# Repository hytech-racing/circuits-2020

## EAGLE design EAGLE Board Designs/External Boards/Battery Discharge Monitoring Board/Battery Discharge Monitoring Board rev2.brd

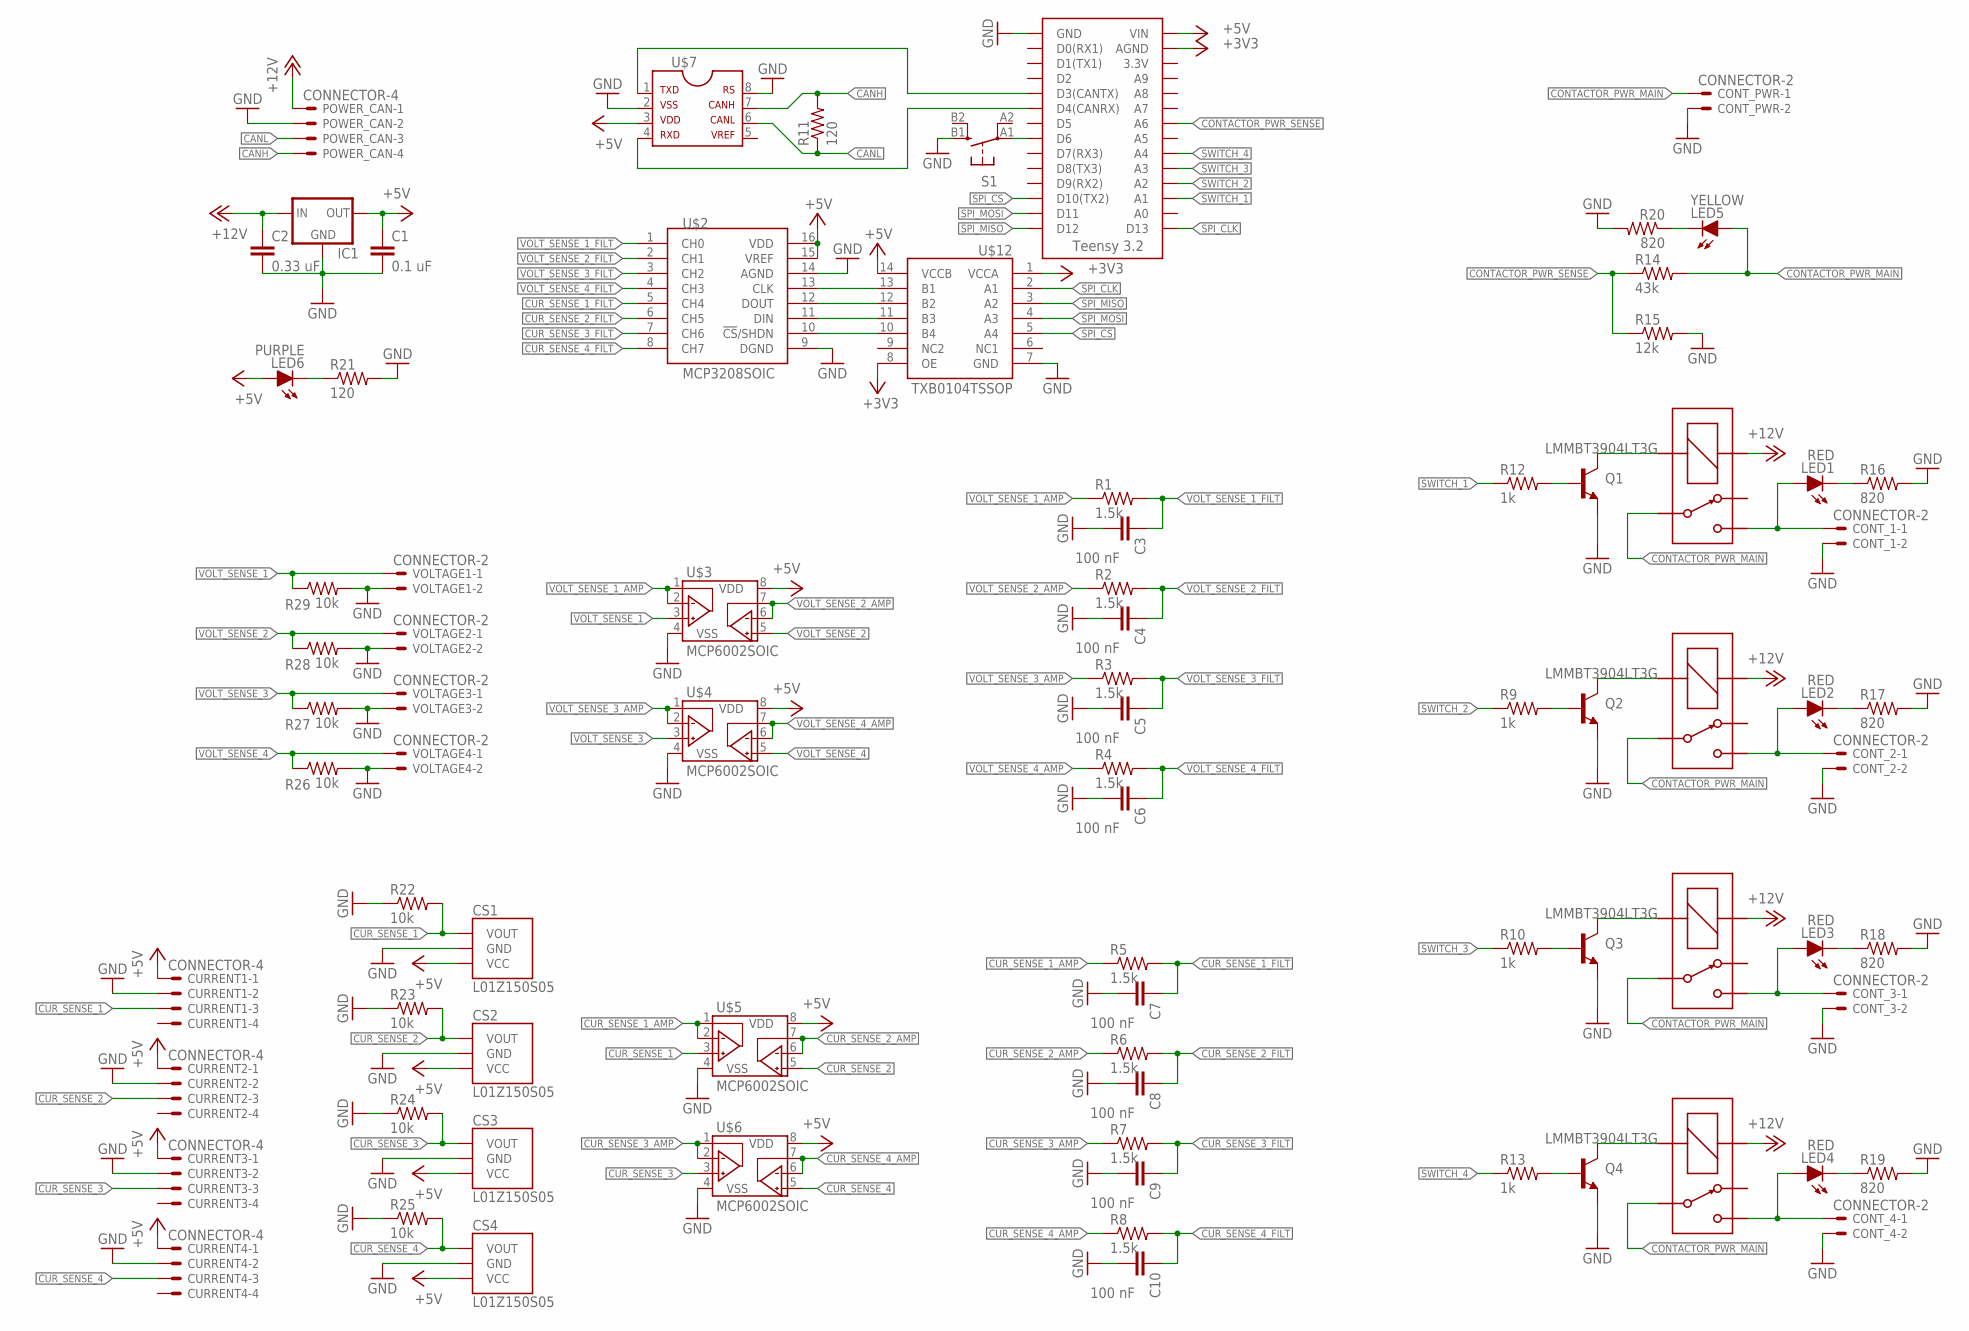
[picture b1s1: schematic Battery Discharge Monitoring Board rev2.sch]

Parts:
C1: 0.1 uF; 0805
C2: 0.33 uF; 0805
C3, C4, C5, C6, C7, C8, C9, C10: 100 nF; 0805
CONT_1, CONT_2, CONT_3, CONT_4: CONNECTOR-2; MINIFIT_5566-2
CONT_PWR: CONNECTOR-2; MINIFIT_5566-2
CS1, CS2, CS3, CS4: L01Z150S05
CURRENT1, CURRENT2, CURRENT3, CURRENT4: CONNECTOR-4; MINIFIT_5566-4
IC1: 5VREG_L7805SPACED; TO-220-SPACED
LED1, LED2, LED3, LED4: RED; LED-805
LED5: YELLOW; LED-805
LED6: PURPLE; LED-805
POWER_CAN: CONNECTOR-4; MINIFIT_5566-4
Q1, Q2, Q3, Q4: LMMBT3904LT3G; SOT23
R1, R2, R3, R4, R5, R6, R7, R8: 1.5k; 0805
R9, R10, R12, R13: 1k; 0805
R11, R21: 120; 0805
R14: 43k; 0805
R15: 12k; 0805
R16, R17, R18, R19, R20: 820; 0805
R22, R23, R24, R25, R26, R27, R28, R29: 10k; 0805
S1: BTN_10-XXSMD; TACTILE_SWITCH_SMD_6.2MM_TALL
U$1: TEENSY_3.2_SIMPLE
U$2: MCP3208SOIC; SOIC-16
U$3, U$4, U$5, U$6: MCP6002SOIC; SOIC-08
U$7: MCP2551; SOIC-08
U$8, U$9, U$10, U$11: G5LE; ZF112
U$12: TXB0104TSSOP; TSSOP-14
VOLTAGE1, VOLTAGE2, VOLTAGE3, VOLTAGE4: CONNECTOR-2; MINIFIT_5566-2

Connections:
+3V3: U$1.AGND, U$12.1 (VCCA), U$12.8 (OE)
+5V: C1.1, CS1.3 (VCC), CS2.3 (VCC), CS3.3 (VCC), CS4.3 (VCC), CURRENT1.1, CURRENT2.1, CURRENT3.1, CURRENT4.1, IC1.3 (OUT), LED6.A, U$1.VIN, U$2.15 (VREF), U$2.16 (VDD), U$3.8 (VDD), U$4.8 (VDD), U$5.8 (VDD), U$6.8 (VDD), U$7.3, U$12.14 (VCCB)
+12V: C2.1, IC1.1 (IN), POWER_CAN.1, U$8.1 (COIL+), U$9.1 (COIL+), U$10.1 (COIL+), U$11.1 (COIL+)
CANH: POWER_CAN.4, R11.2, U$7.7
CANL: POWER_CAN.3, R11.1, U$7.6
CONTACTOR_PWR_1: CONT_1.1, LED1.A, U$8.S
CONTACTOR_PWR_2: CONT_2.1, LED2.A, U$9.S
CONTACTOR_PWR_3: CONT_3.1, LED3.A, U$10.S
CONTACTOR_PWR_4: CONT_4.1, LED4.A, U$11.S
CONTACTOR_PWR_MAIN: CONT_PWR.1, LED5.A, R14.2, U$8.P, U$9.P, U$10.P, U$11.P
CONTACTOR_PWR_SENSE: R14.1, R15.1, U$1.A6
CUR_SENSE_1: CS1.1 (VOUT), CURRENT1.3, R22.2, U$5.3 (VINA+)
CUR_SENSE_1_AMP: R5.1, U$5.1 (VOUTA), U$5.2 (VINA-)
CUR_SENSE_1_FILT: C7.1, R5.2, U$2.5 (CH4)
CUR_SENSE_2: CS2.1 (VOUT), CURRENT2.3, R23.2, U$5.5 (VINB+)
CUR_SENSE_2_AMP: R6.1, U$5.6 (VINB-), U$5.7 (VOUTB)
CUR_SENSE_2_FILT: C8.1, R6.2, U$2.6 (CH5)
CUR_SENSE_3: CS3.1 (VOUT), CURRENT3.3, R24.2, U$6.3 (VINA+)
CUR_SENSE_3_AMP: R7.1, U$6.1 (VOUTA), U$6.2 (VINA-)
CUR_SENSE_3_FILT: C9.1, R7.2, U$2.7 (CH6)
CUR_SENSE_4: CS4.1 (VOUT), CURRENT4.3, R25.2, U$6.5 (VINB+)
CUR_SENSE_4_AMP: R8.1, U$6.6 (VINB-), U$6.7 (VOUTB)
CUR_SENSE_4_FILT: C10.1, R8.2, U$2.8 (CH7)
GND: C1.2, C2.2, C3.2, C4.2, C5.2, C6.2, C7.2, C8.2, C9.2, C10.2, CONT_1.2, CONT_2.2, CONT_3.2, CONT_4.2, CONT_PWR.2, CS1.2 (GND), CS2.2 (GND), CS3.2 (GND), CS4.2 (GND), CURRENT1.2, CURRENT2.2, CURRENT3.2, CURRENT4.2, IC1.2 (GND), POWER_CAN.2, Q1.2 (EMITTER), Q2.2 (EMITTER), Q3.2 (EMITTER), Q4.2 (EMITTER), R15.2, R16.2, R17.2, R18.2, R19.2, R20.2, R21.2, R22.1, R23.1, R24.1, R25.1, R26.2, R27.2, R28.2, R29.2, S1.B1 (S), U$1.GND, U$2.9 (DGND), U$2.14 (AGND), U$3.4 (VSS), U$4.4 (VSS), U$5.4 (VSS), U$6.4 (VSS), U$7.2, U$7.8, U$12.7 (GND), VOLTAGE1.2, VOLTAGE2.2, VOLTAGE3.2, VOLTAGE4.2
unnamed: U$1.D3(CANTX), U$7.1
unnamed: U$1.D4(CANRX), U$7.4
unnamed: Q2.1 (BASE), R9.2
unnamed: Q1.1 (BASE), R12.2
unnamed: Q1.3 (COLLECTOR), U$8.2 (COIL-)
unnamed: Q2.3 (COLLECTOR), U$9.2 (COIL-)
unnamed: Q3.1 (BASE), R10.2
unnamed: Q3.3 (COLLECTOR), U$10.2 (COIL-)
unnamed: Q4.1 (BASE), R13.2
unnamed: Q4.3 (COLLECTOR), U$11.2 (COIL-)
unnamed: LED2.C, R17.1
unnamed: LED1.C, R16.1
unnamed: LED3.C, R18.1
unnamed: LED4.C, R19.1
unnamed: LED5.C, R20.1
unnamed: LED6.C, R21.1
unnamed: U$2.13 (CLK), U$12.13 (B1)
unnamed: U$2.12 (DOUT), U$12.12 (B2)
unnamed: U$2.11 (DIN), U$12.11 (B3)
unnamed: U$2.10 (!CS!/SHDN), U$12.10 (B4)
unnamed: S1.A1, U$1.D6
SPI_CLK: U$1.D13, U$12.2 (A1)
SPI_CS: U$1.D10(TX2), U$12.5 (A4)
SPI_MISO: U$1.D12, U$12.3 (A2)
SPI_MOSI: U$1.D11, U$12.4 (A3)
SWITCH_1: R12.1, U$1.A1
SWITCH_2: R9.1, U$1.A2
SWITCH_3: R10.1, U$1.A3
SWITCH_4: R13.1, U$1.A4
VOLT_SENSE_1: R29.1, U$3.3 (VINA+), VOLTAGE1.1
VOLT_SENSE_1_AMP: R1.1, U$3.1 (VOUTA), U$3.2 (VINA-)
VOLT_SENSE_1_FILT: C3.1, R1.2, U$2.1 (CH0)
VOLT_SENSE_2: R28.1, U$3.5 (VINB+), VOLTAGE2.1
VOLT_SENSE_2_AMP: R2.1, U$3.6 (VINB-), U$3.7 (VOUTB)
VOLT_SENSE_2_FILT: C4.1, R2.2, U$2.2 (CH1)
VOLT_SENSE_3: R27.1, U$4.3 (VINA+), VOLTAGE3.1
VOLT_SENSE_3_AMP: R3.1, U$4.1 (VOUTA), U$4.2 (VINA-)
VOLT_SENSE_3_FILT: C5.1, R3.2, U$2.3 (CH2)
VOLT_SENSE_4: R26.1, U$4.5 (VINB+), VOLTAGE4.1
VOLT_SENSE_4_AMP: R4.1, U$4.6 (VINB-), U$4.7 (VOUTB)
VOLT_SENSE_4_FILT: C6.1, R4.2, U$2.4 (CH3)

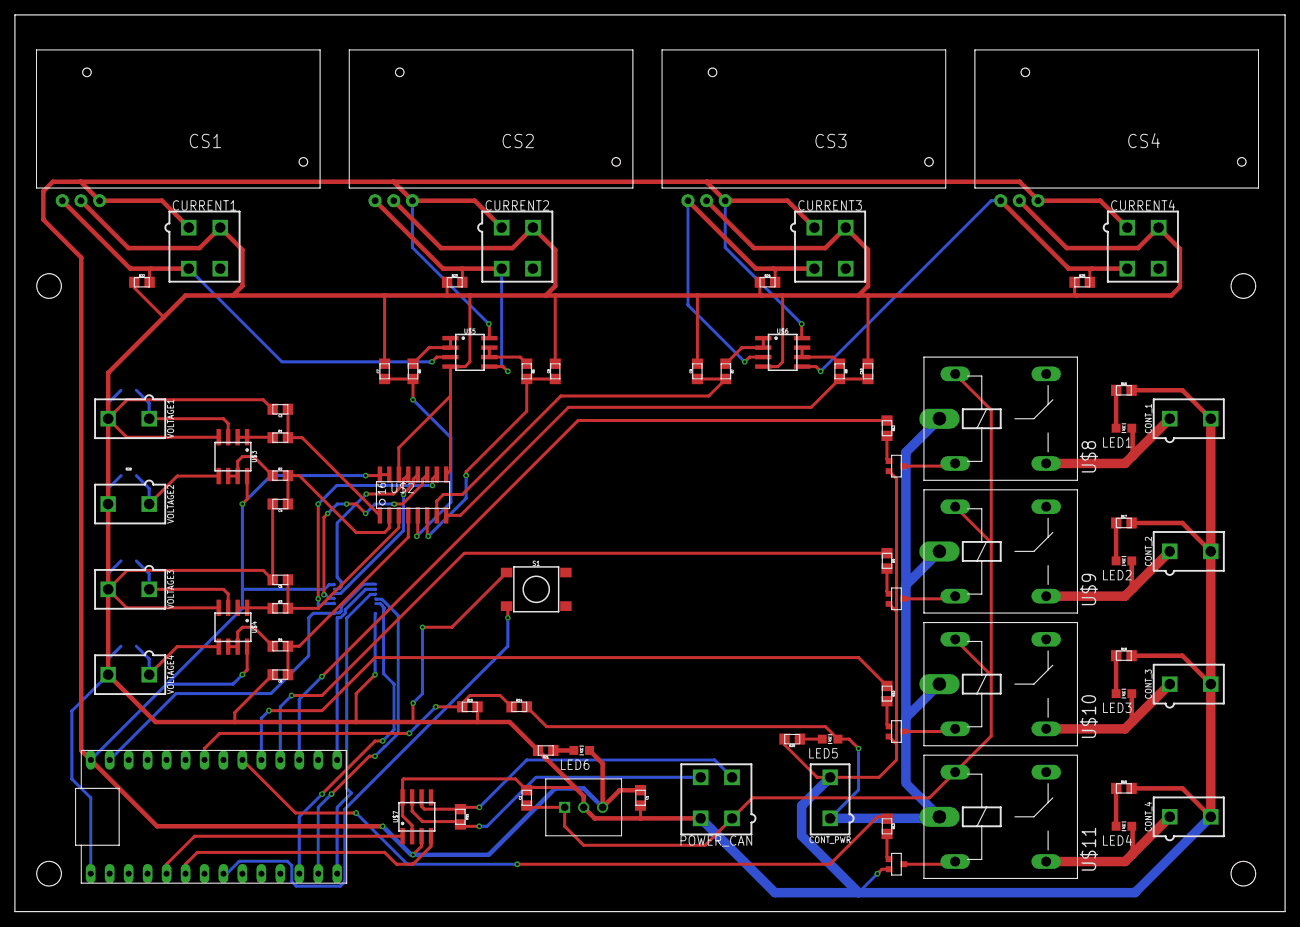
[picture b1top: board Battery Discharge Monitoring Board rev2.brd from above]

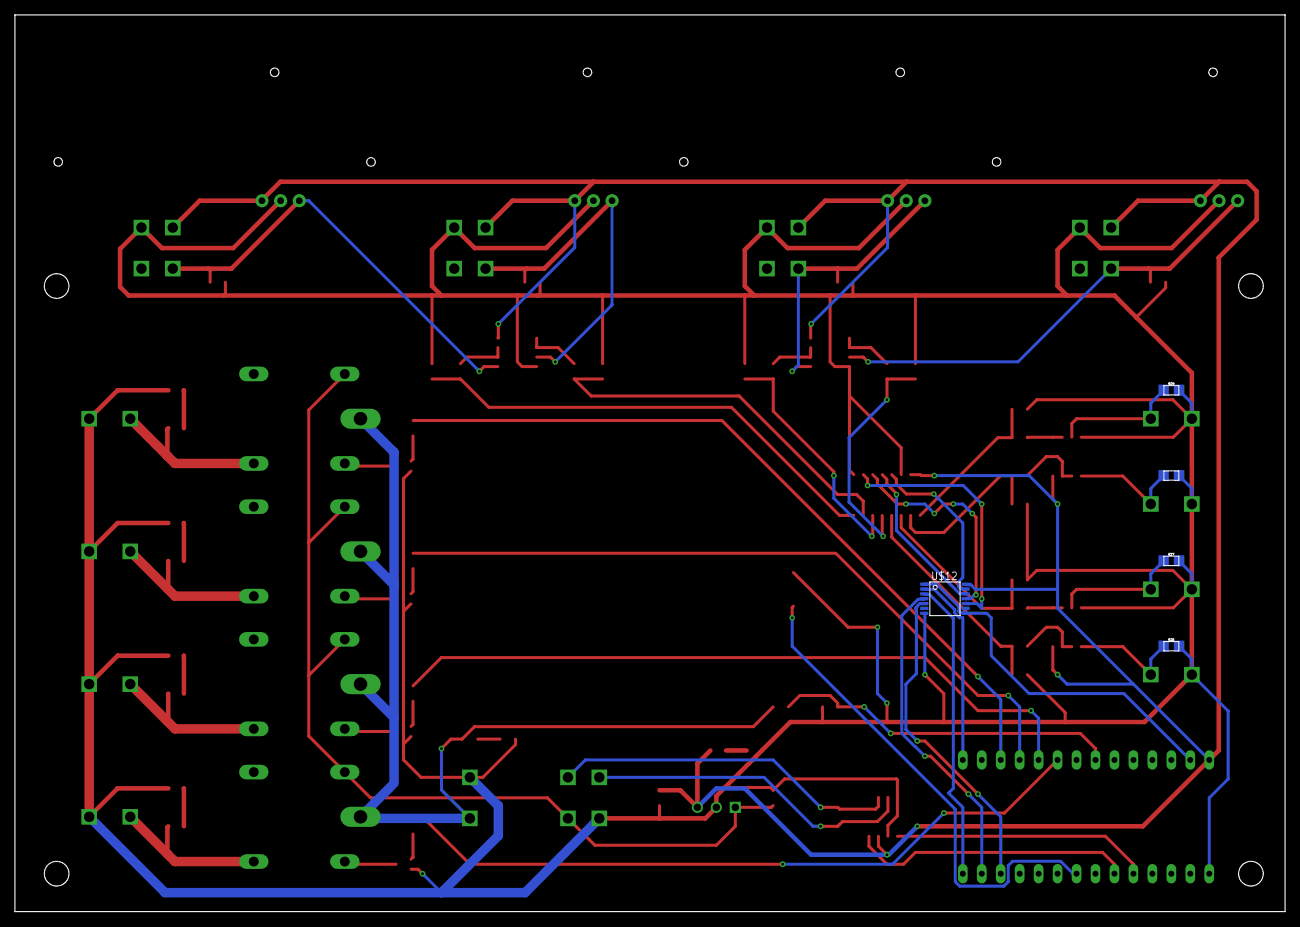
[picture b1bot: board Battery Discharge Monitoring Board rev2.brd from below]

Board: 2 copper layers, 170.2 x 120.1 mm, 81 parts (5 on the bottom side), 65 nets.

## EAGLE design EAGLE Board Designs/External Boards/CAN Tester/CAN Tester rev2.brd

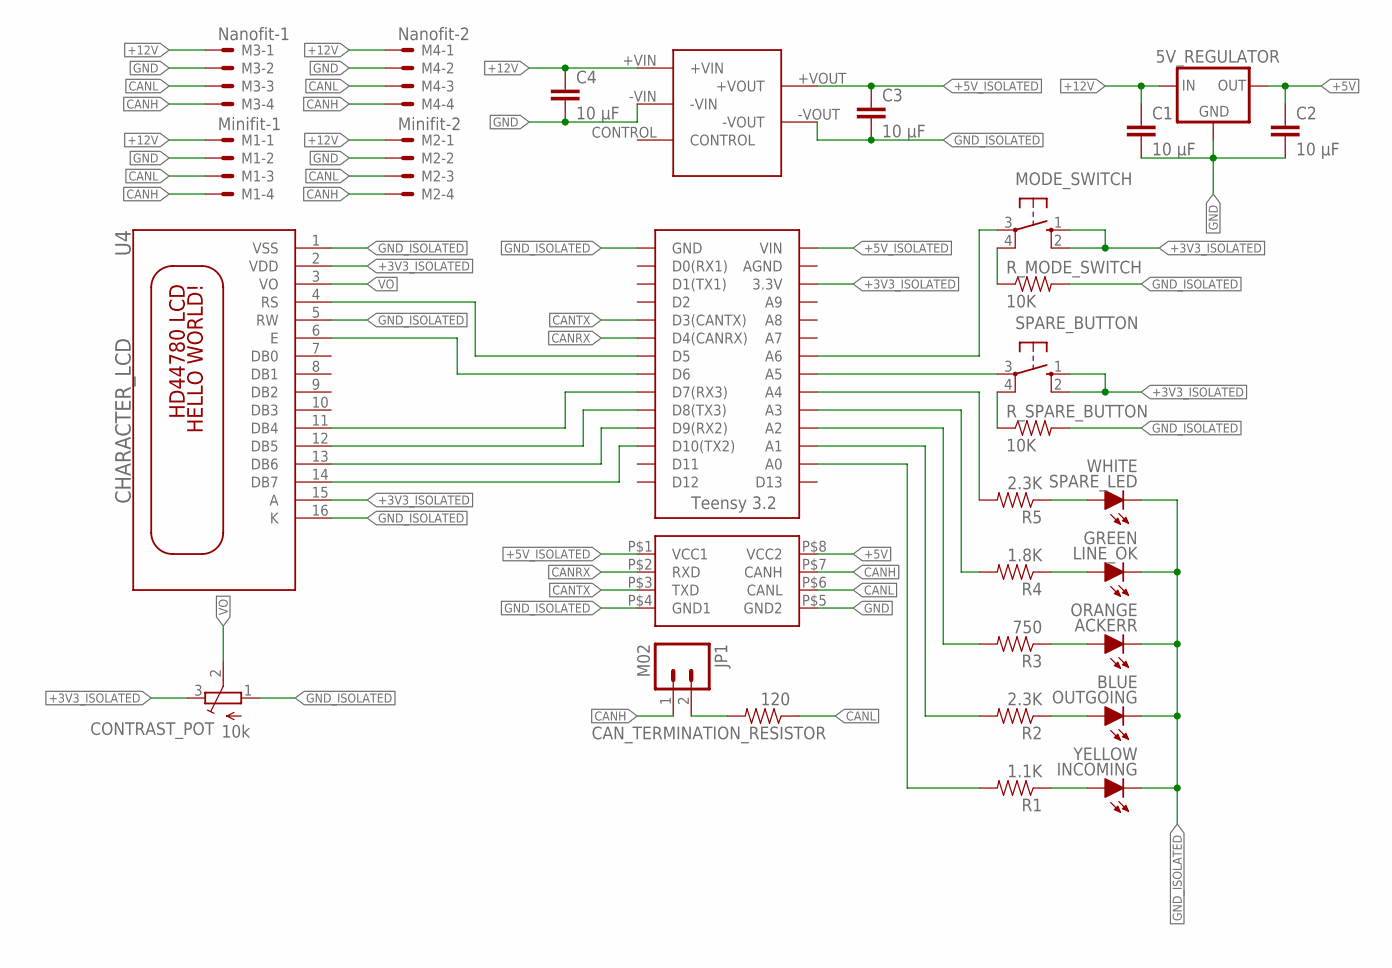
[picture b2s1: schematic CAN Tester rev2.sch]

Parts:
5V_REGULATOR: 5VREG_LM340-NLM340MPX-5.0/NOPB; SOT223
ACKERR: ORANGE; LED-805
C1, C2, C3, C4: 10 μF; 0805
CAN_TERMINATION_RESISTOR: 120; 0805
CONTRAST_POT: 10k; TRIM-3386
INCOMING: YELLOW; LED-805
JP1: M02; 1X02
LINE_OK: GREEN; LED-805
M1: Minifit-1; MINIFIT_5566-4
M2: Minifit-2; MINIFIT_5566-4
M3: Nanofit-1; NANO-FIT_VERTICAL-4
M4: Nanofit-2; NANO-FIT_VERTICAL-4
MODE_SWITCH: BTN_10-XX; B3F-10XX
OUTGOING: BLUE; LED-805
R1: 1.1K; 0805
R2, R5: 2.3K; 0805
R3: 750; 0805
R4: 1.8K; 0805
R_MODE_SWITCH: 10K; 0805
R_SPARE_BUTTON: 10K; 0805
SPARE_BUTTON: BTN_10-XX; B3F-10XX
SPARE_LED: WHITE; LED-805
U1: ISOCAN; DUB8
U3: TEENSY_3.2_SIMPLE
U4: CHARACTER_LCD; LCD1602
U$1: NCS1S1205SC-12V-5VCONVERTER; DCDC-CONVERTER

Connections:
+3V3_ISOLATED: CONTRAST_POT.3 (E), MODE_SWITCH.1 (S), MODE_SWITCH.2 (S1), SPARE_BUTTON.1 (S), SPARE_BUTTON.2 (S1), U3.3.3V, U4.2 (VDD), U4.15 (A)
+5V: 5V_REGULATOR.3 (OUT), C2.1, U1.P$8 (VCC2)
+5V_ISOLATED: C3.1, U1.P$1 (VCC1), U3.VIN, U$1.+VOUT
+12V: 5V_REGULATOR.1 (IN), C1.1, C4.1, M1.1, M2.1, M3.P$1, M4.P$1, U$1.+VIN
CANH: JP1.1, M1.4, M2.4, M3.P$4, M4.P$4, U1.P$7 (CANH)
CANL: CAN_TERMINATION_RESISTOR.1, M1.3, M2.3, M3.P$3, M4.P$3, U1.P$6 (CANL)
CANRX: U1.P$2 (RXD), U3.D4(CANRX)
CANTX: U1.P$3 (TXD), U3.D3(CANTX)
GND: 5V_REGULATOR.2 (GND), 5V_REGULATOR.4 (GND), C1.2, C2.2, C4.2, M1.2, M2.2, M3.P$2, M4.P$2, U1.P$5 (GND2), U$1.-VIN
GND_ISOLATED: ACKERR.C, C3.2, CONTRAST_POT.1 (A), INCOMING.C, LINE_OK.C, OUTGOING.C, R_MODE_SWITCH.2, R_SPARE_BUTTON.2, SPARE_LED.C, U1.P$4 (GND1), U3.GND, U4.1 (VSS), U4.5 (RW), U4.16 (K), U$1.-VOUT
unnamed: R1.2, U3.A0
unnamed: R5.1, SPARE_LED.A
unnamed: SPARE_BUTTON.3, U3.A5
unnamed: R2.2, U3.A1
unnamed: R3.2, U3.A2
unnamed: R4.2, U3.A3
unnamed: R5.2, U3.A4
unnamed: LINE_OK.A, R4.1
unnamed: ACKERR.A, R3.1
unnamed: OUTGOING.A, R2.1
unnamed: INCOMING.A, R1.1
unnamed: MODE_SWITCH.4 (P1), R_MODE_SWITCH.1
unnamed: MODE_SWITCH.3, U3.A6
unnamed: R_SPARE_BUTTON.1, SPARE_BUTTON.4 (P1)
unnamed: CAN_TERMINATION_RESISTOR.2, JP1.2
unnamed: U3.D5, U4.4 (RS)
unnamed: U3.D6, U4.6 (E)
unnamed: U3.D7(RX3), U4.11 (DB4)
unnamed: U3.D8(TX3), U4.12 (DB5)
unnamed: U3.D9(RX2), U4.13 (DB6)
unnamed: U3.D10(TX2), U4.14 (DB7)
VO: CONTRAST_POT.2 (S), U4.3 (VO)

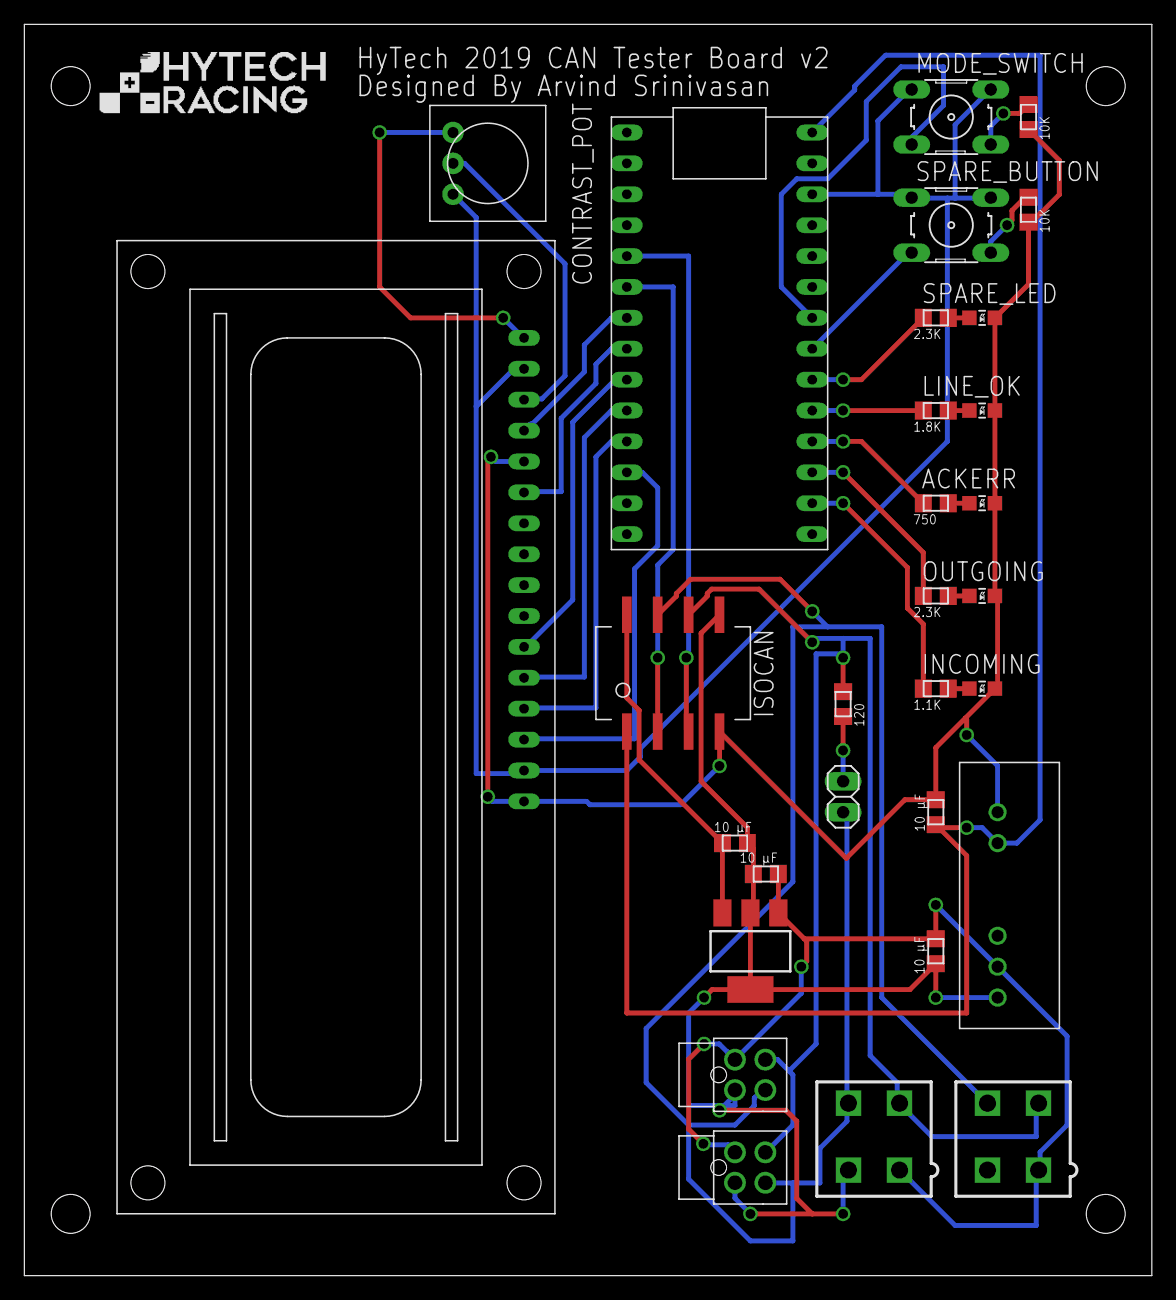
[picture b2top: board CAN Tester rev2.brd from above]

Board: 2 copper layers, 92.7 x 102.9 mm, 30 parts (0 on the bottom side), 32 nets.

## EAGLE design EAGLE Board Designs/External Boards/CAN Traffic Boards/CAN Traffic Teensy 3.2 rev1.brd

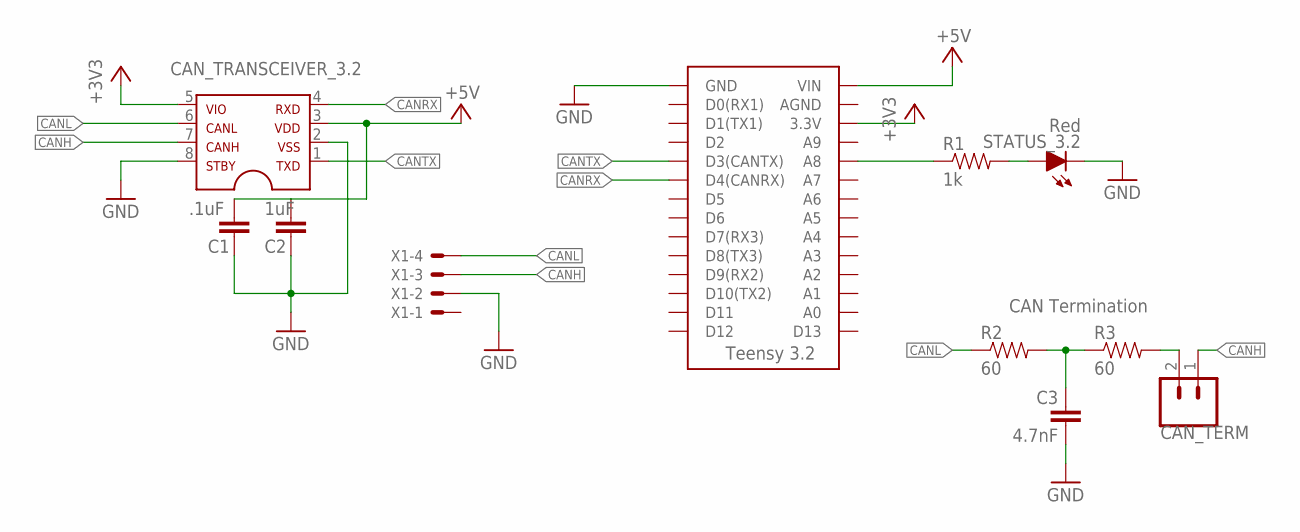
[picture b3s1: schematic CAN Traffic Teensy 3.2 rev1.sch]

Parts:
3.2: TEENSY_3.2_SIMPLE
C1: .1uF; 0603-CAP
C2: 1uF; 0603-CAP
C3: 4.7nF; 0603-CAP
CAN_TERM: M02_SLIM; 1X02_SLIM
CAN_TRANSCEIVER_3.2: MCP2562FDSOIC-08; SOIC-08
R1: 1k; 0603-RES
R2, R3: 60; 0603-RES
STATUS_3.2: Red; LED-603
X1: CONNECTOR-4NANO-FIT_RIGHT_ANGLE-4-SURFACE; NANO-FIT_RIGHT_ANGLE-4-SURFACE

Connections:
+3V3: 3.2.3.3V, CAN_TRANSCEIVER_3.2.5
+5V: 3.2.VIN, C1.1, C2.1, CAN_TRANSCEIVER_3.2.3
CANH: CAN_TERM.1, CAN_TRANSCEIVER_3.2.7, X1.3
CANL: CAN_TRANSCEIVER_3.2.6, R2.1, X1.4
CANRX: 3.2.D4(CANRX), CAN_TRANSCEIVER_3.2.4
CANTX: 3.2.D3(CANTX), CAN_TRANSCEIVER_3.2.1
GND: 3.2.GND, C1.2, C2.2, C3.2, CAN_TRANSCEIVER_3.2.2, CAN_TRANSCEIVER_3.2.8, STATUS_3.2.C, X1.2
unnamed: C3.1, R2.2, R3.1
unnamed: 3.2.A8, R1.1
unnamed: R1.2, STATUS_3.2.A
unnamed: CAN_TERM.2, R3.2

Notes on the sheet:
CAN Termination

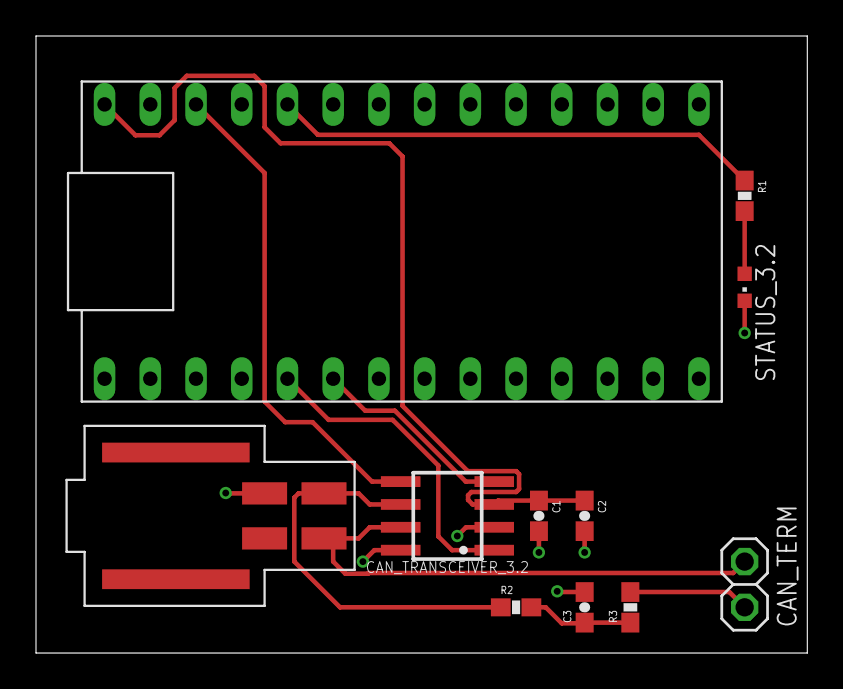
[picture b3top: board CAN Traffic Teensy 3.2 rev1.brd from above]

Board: 2 copper layers, 42.9 x 34.3 mm, 11 parts (0 on the bottom side), 11 nets.

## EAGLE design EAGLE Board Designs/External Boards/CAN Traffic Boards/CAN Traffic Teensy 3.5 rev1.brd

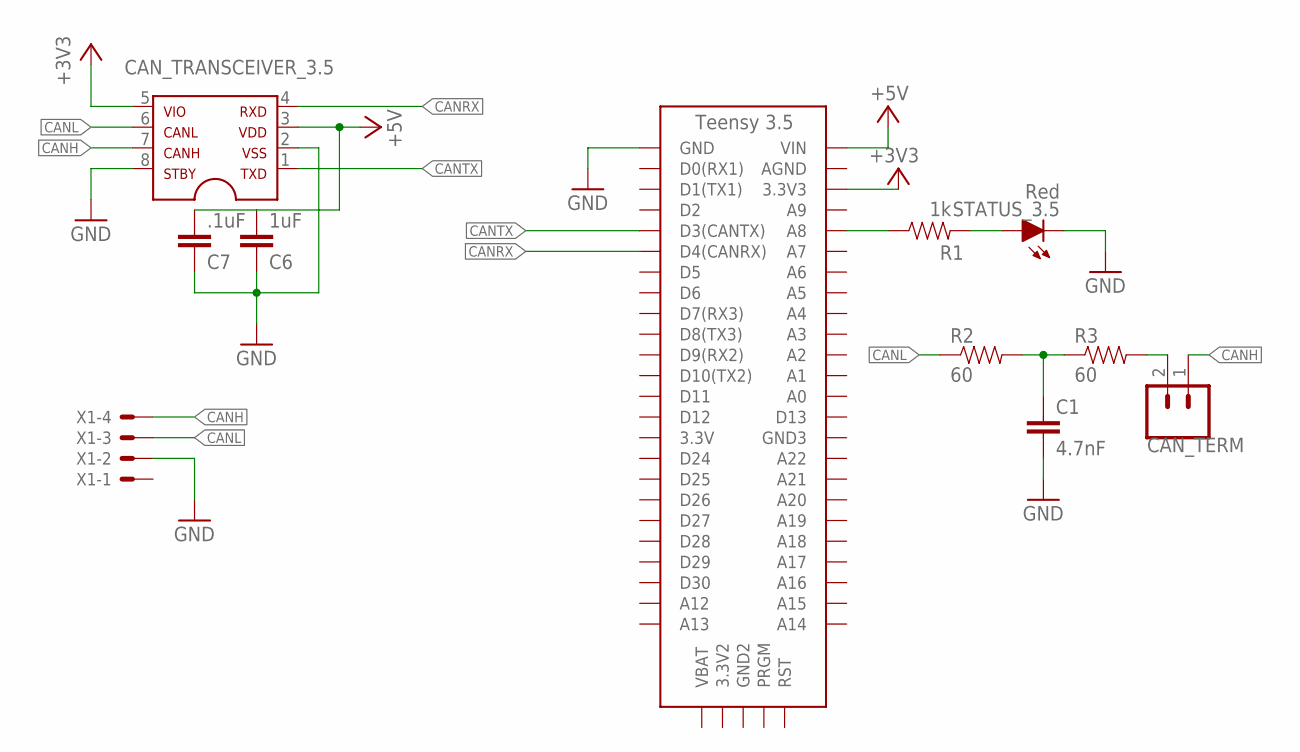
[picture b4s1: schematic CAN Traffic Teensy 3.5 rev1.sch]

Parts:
3.5: TEENSY_3.5_EXT_RTC
C1: 4.7nF; 0603-CAP
C6: 1uF; 0603-CAP
C7: .1uF; 0603-CAP
CAN_TERM: M02_SLIM; 1X02_SLIM
CAN_TRANSCEIVER_3.5: MCP2562SOIC-08; SOIC-08
R1: 1k; 0603-RES
R2, R3: 60; 0603-RES
STATUS_3.5: Red; LED-603
X1: CONNECTOR-4NANO-FIT_RIGHT_ANGLE-4-SURFACE; NANO-FIT_RIGHT_ANGLE-4-SURFACE

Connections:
+3V3: 3.5.3.3V3, CAN_TRANSCEIVER_3.5.5
+5V: 3.5.VIN, C6.1, C7.1, CAN_TRANSCEIVER_3.5.3
CANH: CAN_TERM.1, CAN_TRANSCEIVER_3.5.7, X1.4
CANL: CAN_TRANSCEIVER_3.5.6, R2.1, X1.3
CANRX: 3.5.D4(CANRX), CAN_TRANSCEIVER_3.5.4
CANTX: 3.5.D3(CANTX), CAN_TRANSCEIVER_3.5.1
GND: 3.5.GND, C1.2, C6.2, C7.2, CAN_TRANSCEIVER_3.5.2, CAN_TRANSCEIVER_3.5.8, STATUS_3.5.C, X1.2
unnamed: 3.5.A8, R1.1
unnamed: C1.1, R2.2, R3.1
unnamed: R1.2, STATUS_3.5.A
unnamed: CAN_TERM.2, R3.2

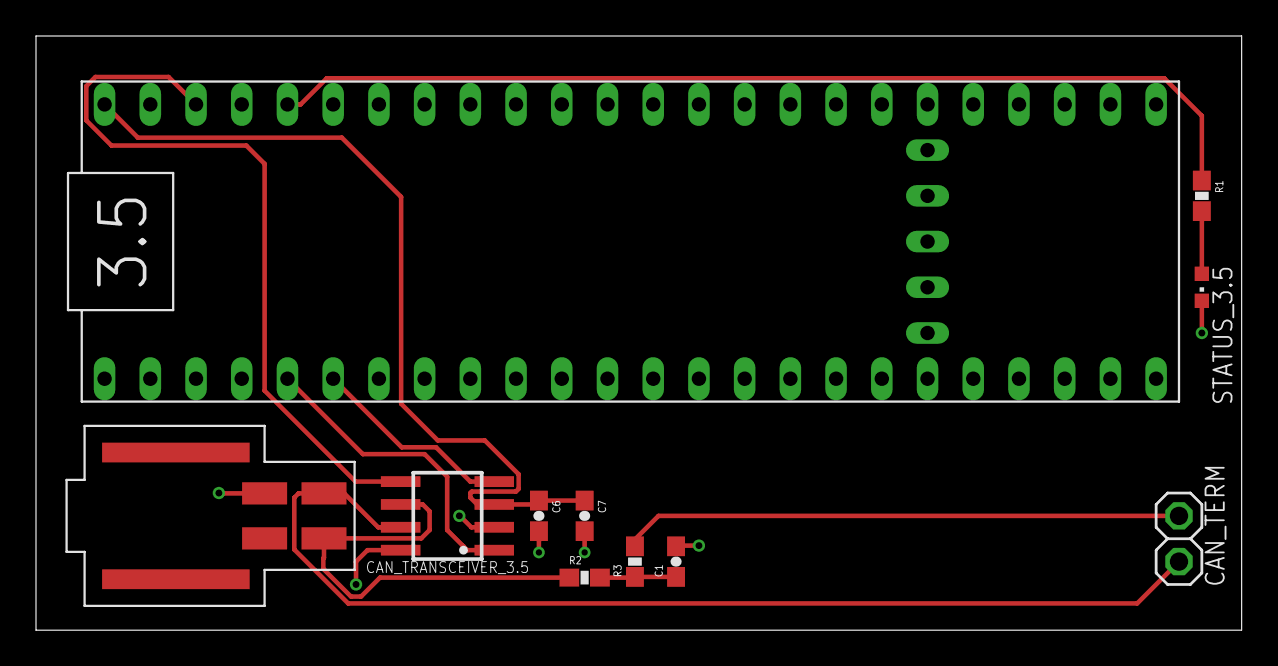
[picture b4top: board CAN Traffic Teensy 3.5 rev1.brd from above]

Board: 2 copper layers, 67.0 x 33.0 mm, 11 parts (0 on the bottom side), 11 nets.

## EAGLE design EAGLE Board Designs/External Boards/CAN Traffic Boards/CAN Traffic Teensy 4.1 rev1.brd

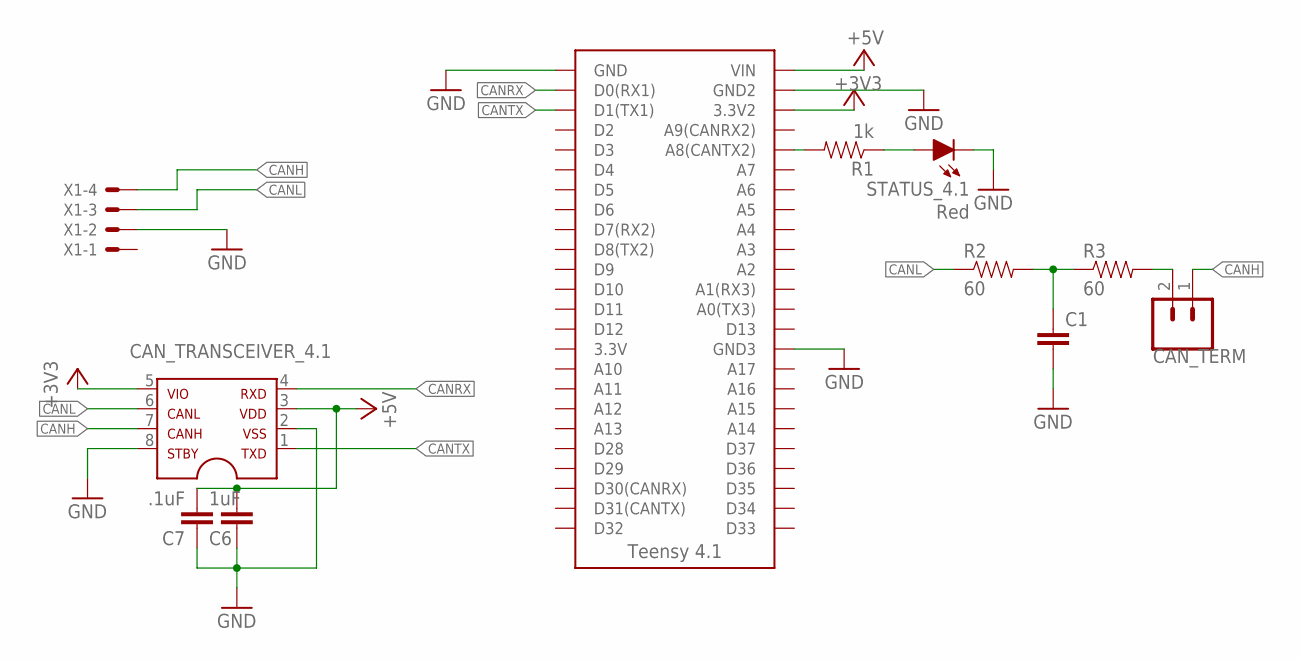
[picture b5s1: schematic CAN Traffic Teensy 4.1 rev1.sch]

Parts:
4.1: TEENSY_4.1_SIMPLE
C1: CAP0603-CAP; 0603-CAP
C6: 1uF; 0603-CAP
C7: .1uF; 0603-CAP
CAN_TERM: M02_SLIM; 1X02_SLIM
CAN_TRANSCEIVER_4.1: MCP2562SOIC-08; SOIC-08
R1: 1k; 0603-RES
R2, R3: 60; 0603-RES
STATUS_4.1: Red; LED-603
X1: CONNECTOR-4NANO-FIT_RIGHT_ANGLE-4-SURFACE; NANO-FIT_RIGHT_ANGLE-4-SURFACE

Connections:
+3V3: 4.1.3.3V2, CAN_TRANSCEIVER_4.1.5
+5V: 4.1.VIN, C6.1, C7.1, CAN_TRANSCEIVER_4.1.3
CANH: CAN_TERM.1, CAN_TRANSCEIVER_4.1.7, X1.4
CANL: CAN_TRANSCEIVER_4.1.6, R2.1, X1.3
CANRX: 4.1.D0(RX1), CAN_TRANSCEIVER_4.1.4
CANTX: 4.1.D1(TX1), CAN_TRANSCEIVER_4.1.1
GND: 4.1.GND, 4.1.GND2, 4.1.GND3, C1.2, C6.2, C7.2, CAN_TRANSCEIVER_4.1.2, STATUS_4.1.C, X1.2
unnamed: 4.1.A8(CANTX2), R1.2
unnamed: R1.1, STATUS_4.1.A
unnamed: C1.1, R2.2, R3.1
unnamed: CAN_TERM.2, R3.2

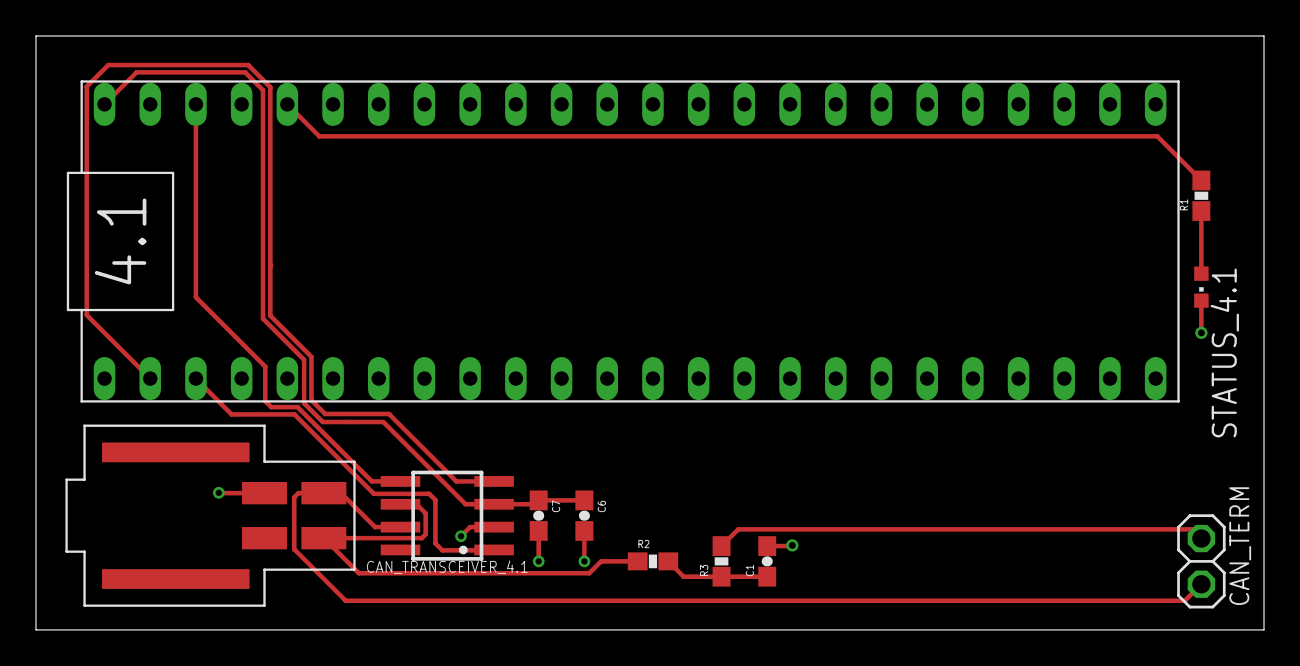
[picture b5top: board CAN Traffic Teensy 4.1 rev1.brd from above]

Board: 2 copper layers, 68.2 x 33.0 mm, 11 parts (0 on the bottom side), 11 nets.

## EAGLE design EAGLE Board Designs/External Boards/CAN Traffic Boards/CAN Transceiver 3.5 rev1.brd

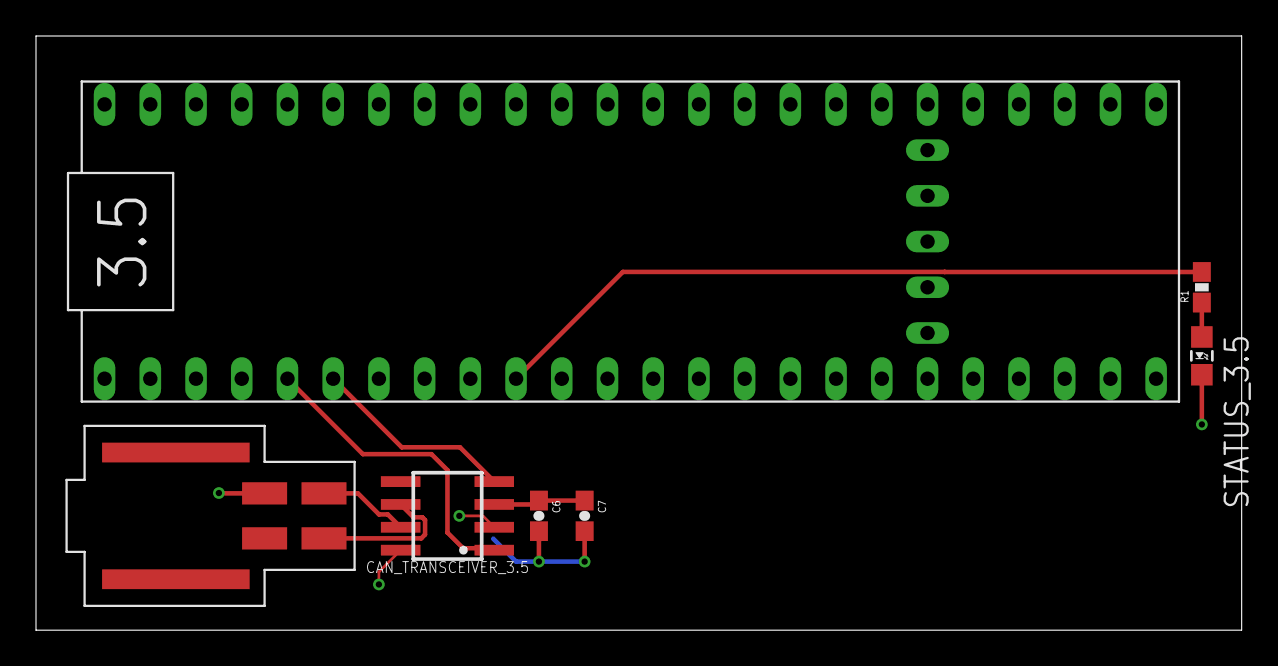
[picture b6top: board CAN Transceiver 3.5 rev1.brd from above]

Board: 2 copper layers, 67.0 x 33.0 mm, 7 parts (0 on the bottom side), 8 nets.

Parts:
C6: 1uF; 0603-CAP
C7: .1uF; 0603-CAP
CAN_TRANSCEIVER_3.5: MCP2562SOIC-08; SOIC-08
R1: 1k; 0603-RES
STATUS_3.5: Red; LED-805
U$1: TEENSY_3.5_EXT_RTC
X1: CONNECTOR-4NANO-FIT_RIGHT_ANGLE-4-SURFACE; NANO-FIT_RIGHT_ANGLE-4-SURFACE

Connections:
+5V: C6.1, C7.1, CAN_TRANSCEIVER_3.5.3
CANH: CAN_TRANSCEIVER_3.5.7, X1.4
CANL: CAN_TRANSCEIVER_3.5.6, X1.3
GND: C6.2, C7.2, CAN_TRANSCEIVER_3.5.2, CAN_TRANSCEIVER_3.5.8, STATUS_3.5.C, U$1.GND, X1.2
unnamed: CAN_TRANSCEIVER_3.5.4, U$1.D4(CANRX)
unnamed: CAN_TRANSCEIVER_3.5.1, U$1.D3(CANTX)
unnamed: R1.1, STATUS_3.5.A
unnamed: R1.2, U$1.D8(TX3)
